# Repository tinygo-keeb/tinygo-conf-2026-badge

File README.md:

# TinyGo Conf 2026 Badge

[English](README.en.md)

TinyGo Conference 2026 向けバッジのハードウェア設計と TinyGo ファームウェアをまとめたリポジトリです。ESP32-S3-DevKit を中心に、ディスプレイ、入力デバイス、音声、赤外線、温湿度センサーなどを搭載しています。

## 主な機能

| 機能 | ハードウェア | ファームウェアの例 |
| --- | --- | --- |
| 表示 | ST7789 ディスプレイ | [`display`](firmware/examples/display)、[`demo`](firmware/examples/demo) |
| 入力 | ジョイスティック、スイッチ × 2 | [`input`](firmware/examples/input)、[`rhythm`](firmware/examples/rhythm) |
| 光と音 | RGB LED × 2、MAX98357 アンプとスピーカー | [`blink`](firmware/examples/blink)、[`audio`](firmware/examples/audio) |
| センサー・拡張 | AHT21B 温湿度センサー、Grove 互換 I2C コネクタ | [`aht21b`](firmware/examples/aht21b)、[`i2cscan`](firmware/examples/i2cscan) |
| 赤外線 | 赤外線 LED・受信モジュール | [`ir`](firmware/examples/ir)、[`irlearn`](firmware/examples/irlearn) |
| 無線通信 | ESP32-S3 の Wi-Fi・BLE | [`wifi-server`](firmware/examples/wifi-server)、[`ble-sensor`](firmware/examples/ble-sensor) |

全体の動作確認には [`selftest`](firmware/examples/selftest) を使えます。

## 組み立て

必要な部品と写真付きの組み立て手順は [ビルドガイド](hardware/build/build.md) を参照してください。

## ドキュメントとファイル

| パス | 内容 |
| --- | --- |
| [hardware/README.md](hardware/README.md) | 基板の構成、KiCad のセットアップ、製造データ |
| [hardware/build/build.md](hardware/build/build.md) | 部品一覧と写真付きの組み立て手順 |
| [conf2026badge case](https://makerworld.com/models/3438451) | 3D プリント用のケースデータ (MakerWorld) |
| [hardware/tinygo-conf-2026.kicad_pro](hardware/tinygo-conf-2026.kicad_pro) | KiCad プロジェクト。回路図と基板レイアウトは同じディレクトリにあります |
| [firmware/README.md](firmware/README.md) | ビルド・書き込み方法、サンプル一覧、ピン割り当て、実装上の注意点 |
| [firmware/Makefile](firmware/Makefile) | サンプルのビルド確認や Wi-Fi サンプルの書き込み |

## 使い始める

### ハードウェア

KiCad 9.0 以降を使用します。KiCad ライブラリの一部はサブモジュールなので、リポジトリのルートで取得してください。

```sh
git submodule update --init --recursive
```

[KiCad プロジェクト](hardware/tinygo-conf-2026.kicad_pro) を開き、バッジの組み立てには [組み立てガイド](hardware/build/build.md) を参照してください。

### ファームウェア

TinyGo を用意し、ESP32-S3-DevKit を接続して以下を実行します。

```sh
cd firmware
tinygo flash --target esp32s3-box-3 --size short ./examples/blink
tinygo monitor --target esp32s3-box-3
```

全サンプルのビルド確認は `firmware/` で `make smoketest` を実行します。Wi-Fi・BLE の設定や各サンプルの使い方は [ファームウェアのREADME](firmware/README.md) を参照してください。

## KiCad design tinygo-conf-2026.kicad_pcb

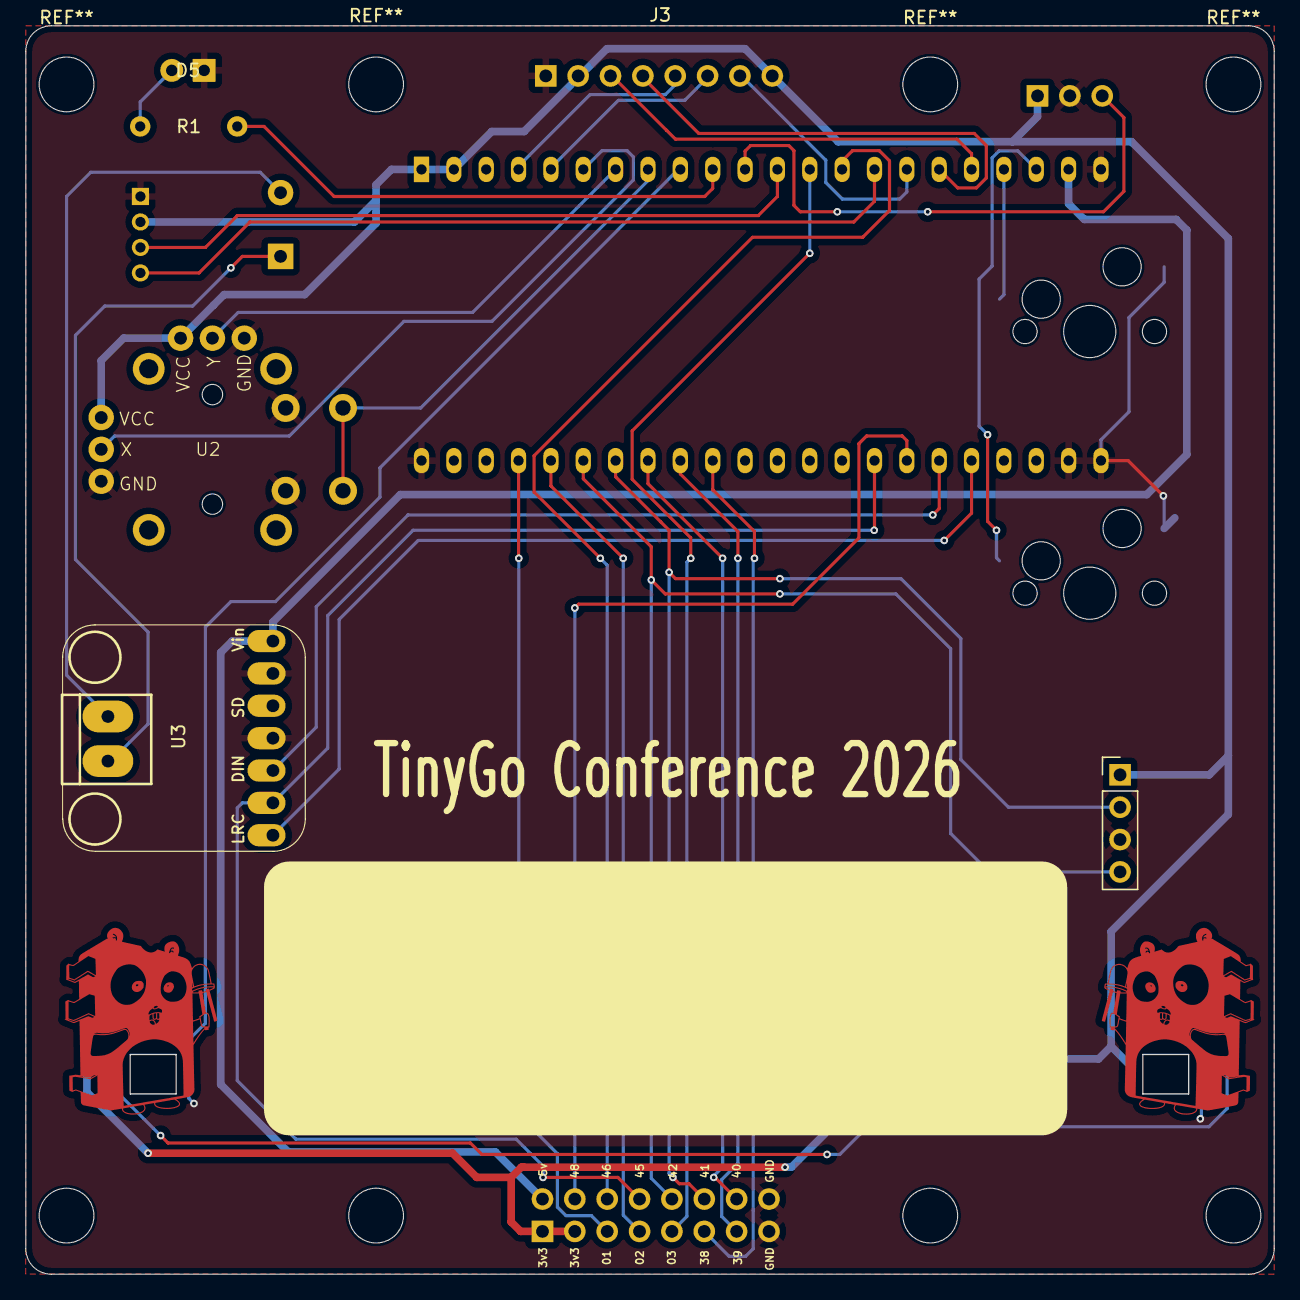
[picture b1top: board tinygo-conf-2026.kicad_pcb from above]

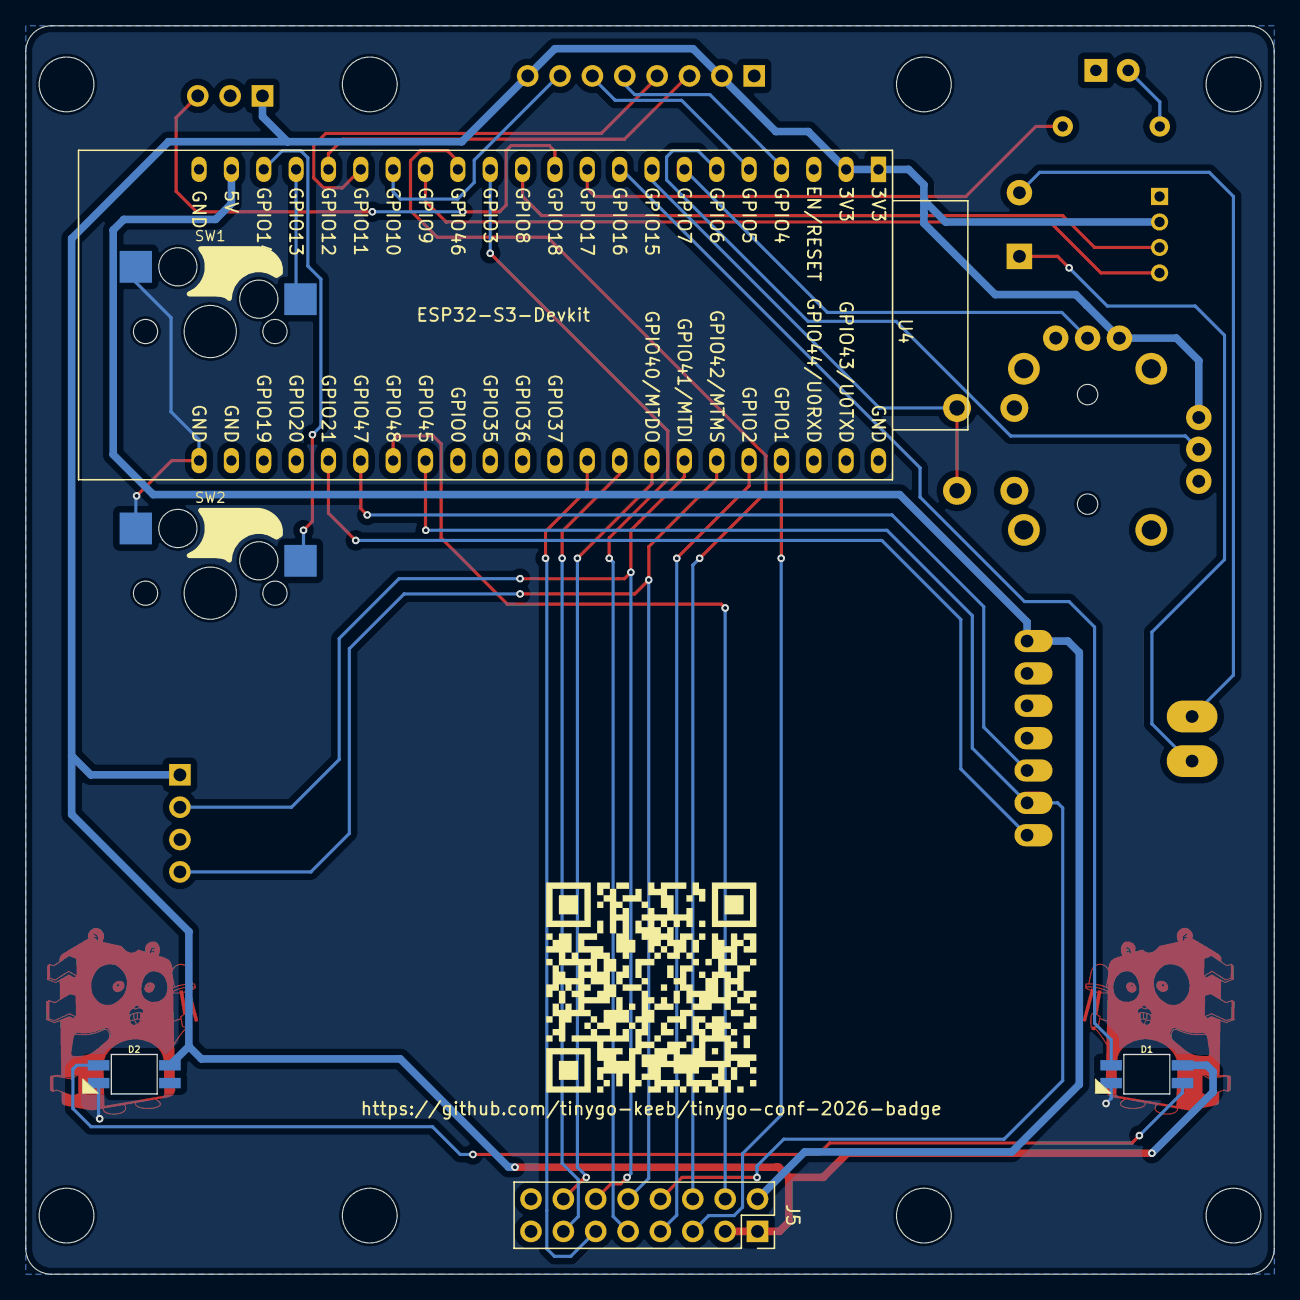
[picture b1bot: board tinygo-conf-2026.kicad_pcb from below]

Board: 2 copper layers, 98.0 x 98.0 mm, 16 parts (7 on the bottom side), 35 nets.

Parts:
D1, D2: WS2812B; YS-SK6812MINI-E
D5: LED; LED_D3.0mm_Clear
J1: Conn_01x04_Pin; PinHeader_1x04_P2.00mm_Vertical
J2: Conn_01x03_Pin; PinHeader_1x03_P2.54mm_Vertical
J3: Conn_01x08_Pin; ST7789_1.3_240x240_LCD_Module
J4: AHT21B; PinHeader_1x04_P2.54mm_Vertical
J5: Conn_02x08_Counter_Clockwise; PinSocket_2x08_P2.54mm_Vertical
LS1: Speaker; Buzzer_TDK_PS1240P02BT_D12.2mm_H6.5mm
QR*****: https://github.com/tinygo-keeb/tinygo-conf-2026-b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; tinygo-conf-badge-qr-code
R1: R; R_Axial_DIN0207_L6.3mm_D2.5mm_P7.62mm_Horizontal
SW1, SW2: SW_Push; keyswitch_cherrymx_hotswap_1u
U2: RKJXV122400R
U3: adafruit-MAX98357
U4: ESP32-S3-Devkit; ESP32-S3-DevKitC

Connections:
/3V3: D1.1 (VDD), D2.1 (VDD), J1.2, J2.1, J3.2, J3.8, J4.1, J5.1, J5.2, U2.3 (VR1-3), U2.4 (VR2-1), U4.1 (3V3), U4.2 (3V3)
/BCLK: J5.13, U3.6 (BCLK), U4.30 (GPIO45)
/CS: J3.7, U4.16 (GPIO10)
/DC: J3.6, U4.5 (GPIO5)
/DIN: U3.5 (DIN), U4.28 (GPIO47)
/GPIO1: J5.3, U4.41 (GPIO1)
/GPIO2: J5.4, U4.40 (GPIO2)
/GPIO3: J5.5, U4.13 (GPIO3)
/GPIO38: J5.6, U4.35 (GPIO38)
/GPIO39: J5.7, U4.36 (GPIO39/MTCK)
/GPIO40: J5.10, U4.37 (GPIO40/MTDO)
/GPIO41: J4.2, J5.11, U4.38 (GPIO41/MTDI)
/GPIO42: J4.4, J5.12, U4.39 (GPIO42/MTMS)
/GPIO46: J5.14, U4.14 (GPIO46)
/GPIO48: J5.15, U4.29 (GPIO48)
/I2C_SCL: J1.4, U4.15 (GPIO9)
/I2C_SDA: J1.3, U4.12 (GPIO8)
/IR_DATA: J2.3, U4.11 (GPIO18)
/IR_LED: R1.1, U4.10 (GPIO17)
/LED: D1.4 (DIN), U4.9 (GPIO16)
/LRC: U3.7 (LRC), U4.27 (GPIO21)
/RES: J3.5, U4.4 (GPIO4)
/SCL: J3.3, U4.18 (GPIO12)
/SDA: J3.4, U4.17 (GPIO11)
/SW1: SW1.1, U4.19 (GPIO13)
/SW2: SW2.1, U4.20 (GPIO14)
/VR_BTN: U2.8 (SW-b), U4.8 (GPIO15)
/VR_X: U2.2 (VR1-2), U4.7 (GPIO7)
/VR_Y: U2.5 (VR2-2), U4.6 (GPIO6)
GND: D1.3 (VSS), D2.3 (VSS), D5.1 (K), J1.1, J2.2, J3.1, J4.3, J5.8, J5.9, SW1.2, SW2.2, U2.1 (VR1-1), U2.6 (VR2-3), U2.7 (SW-a), U3.2 (GND), U3.4 (GAIN), U4.22 (GND), U4.23 (GND), U4.24 (GND), U4.44 (GND)
unnamed: D1.2 (DOUT), D2.4 (DIN)
unnamed: D5.2 (A), R1.2
unnamed: LS1.2, U3.9 (OUTN)
unnamed: LS1.1, U3.8 (OUTP)
VCC: J5.16, U3.1 (Vin), U4.21 (5V)
